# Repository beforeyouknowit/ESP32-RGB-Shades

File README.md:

# ESP32 RGB Shades

This repo currently represents an electronics update, based on the  ESP32 Pico Mini, as a redesign of [macetech/RGBShades](https://github.com/macetech/RGBShades) from 2015.

I was one of the Kickstarter backers of macetech's original campaign for "RGB Shades", described here: https://www.kickstarter.com/projects/macetech/rgb-led-shades

Redesigned in KiCad 8.x, based on original Eagle files from Macetech's website.

## Features
New electronics include:
- USB-C PD via STUSB4500 IC, which negotiates with USB-C PD supplies (e.g. modern power bank batteries and wall adapters) for 20V output, up to 5A, or 100W.
- TDK ICS-43434 microphone, with I2S digital output, for onboard audio analysis and beat detection.
- Jumper for selecting microphone digital output as left (default) or right channel audio over I2S.
- 5V, 1.5A linear voltage regulator for powering WS2812B LEDs from 20V USB-C PD supply.
- 3.3V, 1.0A linear voltage regulator for powering onboard ICs.
- Slight changes to rear ear-stem geometry to accommodate new USB-C PD IC and passives.

What hasn't changed:
- Same power switch.
- Same pushbuttons. (Now labeled as "Animate" and "Brightness".)
- Same CP2102N USB to UART, with "full remote reset" capabilities, making firmware flashing just as easy.
- Same 0.1" (DuPont connector/header) through-holes for direct CP2102N debug, e.g. for bypassing USB.
- Same JST connector to existing RGBShades display, i.e. the front part of the glasses assembly.
- Same glasses assembly hardware positions; meant as a direct upgrade for existing RGBShades owners.

## License
This project is licensed under CERN-OHL-S 2.0 or later version. See the LICENSE file for details.

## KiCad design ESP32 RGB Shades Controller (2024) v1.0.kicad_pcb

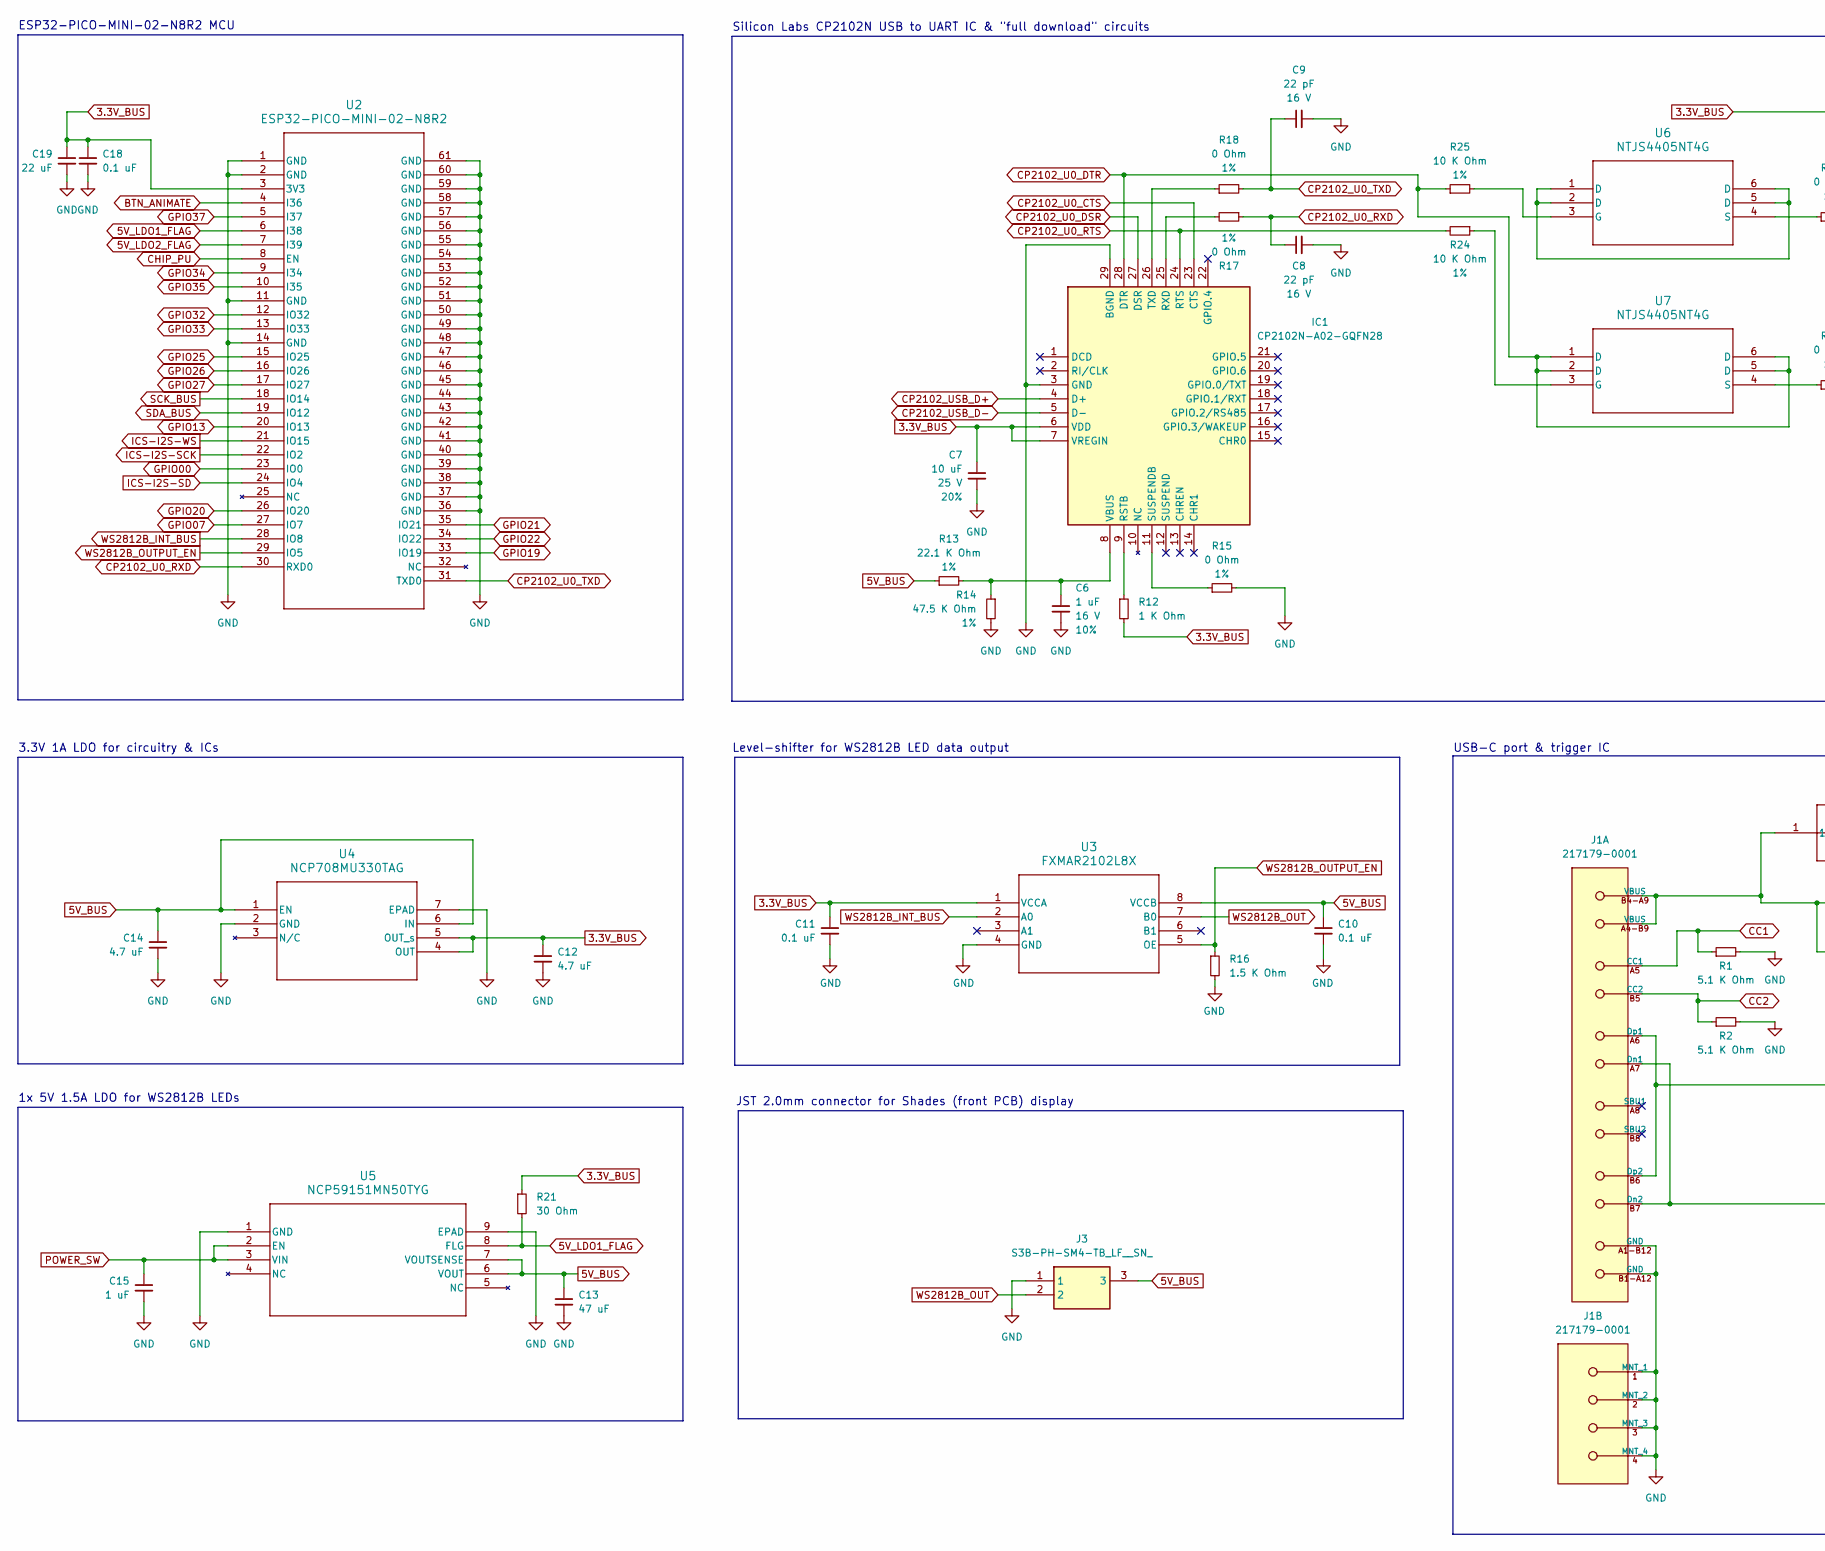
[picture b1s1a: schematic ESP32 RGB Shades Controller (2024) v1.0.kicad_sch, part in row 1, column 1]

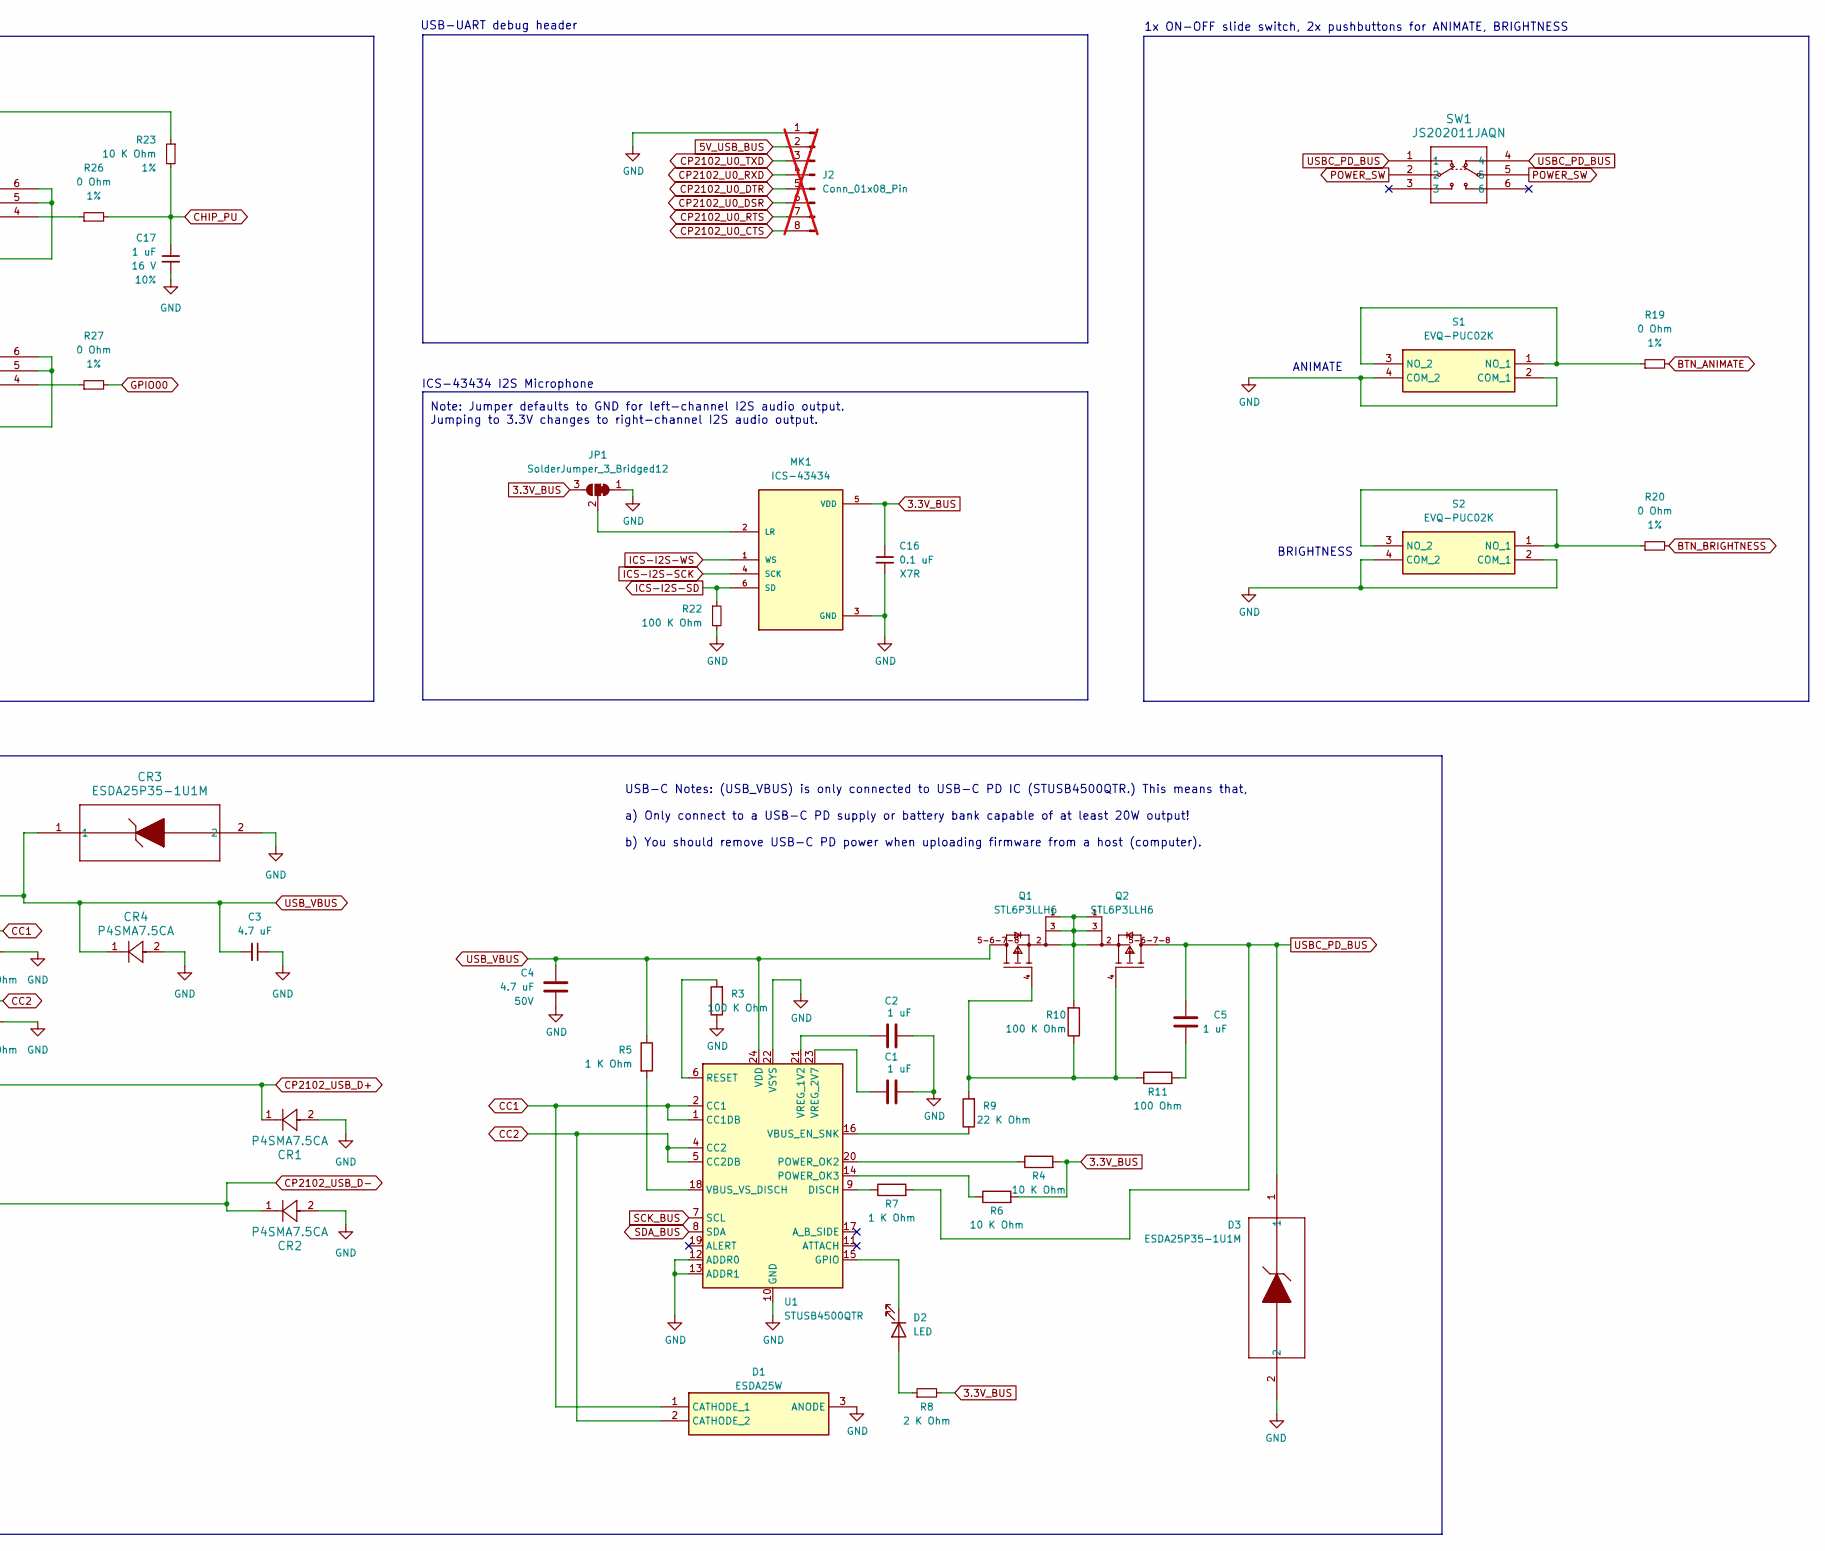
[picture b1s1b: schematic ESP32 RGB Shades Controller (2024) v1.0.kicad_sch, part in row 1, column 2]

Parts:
C1, C2, C5: 1 uF; C_0805_2012Metric; MPN1 CC0805KRX7R7BB104
C3, C12, C14: 4.7 uF; C_0805_2012Metric
C4: 4.7 uF; C_0805_2012Metric; Voltage 50V; MPN1 CC0805KRX7R7BB104
C6, C17: 1 uF; C_0805_2012Metric; Voltage 16 V; Tolerance 10%
C7: 10 uF; C_0805_2012Metric; Voltage 25 V; Tolerance 20%
C8, C9: 22 pF; C_0805_2012Metric; Voltage 16 V
C10, C11, C16, C18: 0.1 uF; C_0805_2012Metric
C13: 47 uF; C_0805_2012Metric
C15: 1 uF; C_0805_2012Metric
C19: 22 uF; C_0805_2012Metric
CR1, CR2, CR4: P4SMA7.5CA; P4SMASeries_LTF
CR3: ESDA25P35-1U1M; ESDA25P351U1M
D1: ESDA25W; SOT323-3L_STM; Manufacturer_Part_Number ESDA25W; Mouser Part Number 511-ESDA25W
D2: LED; LED_0805_2012Metric
D3: ESDA25P35-1U1M; ESDA25P351U1M; Manufacturer_Part_Number ESDA25P35-1U1M; Mouser Part Number 511-ESDA25P35-1U1M
IC1: CP2102N-A02-GQFN28; QFN50P500X500X80-29N-D; Manufacturer_Part_Number CP2102N-A02-GQFN28; Mouser Part Number 634-CP2102NA02GQFN28
J1: 217179-0001; Molex-217179-0001-MFG; current rating 1.25A; voltage rating 30V; mouser part number 538-217179-0001; digikey description CONN RCP USB2.0 TYP C 24P SMD RA
J2: Conn_01x08_Pin; PinHeader_1x08_P2.54mm_Vertical; not fitted
J3: S3B-PH-SM4-TB_LF__SN_; S3B-PH-SM4-TB; Manufacturer_Part_Number S3B-PH-SM4-TB(LF)(SN)
JP1: SolderJumper_3_Bridged12; SolderJumper-3_P1.3mm_Bridged2Bar12_Pad1.0x1.5mm_NumberLabe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
MK1: ICS-43434; MIC_ICS-43434
Q1, Q2: STL6P3LLH6; STMicroelectronics-PowerFLAT3.3x3.3-8465286-0-2-MFG; mouser part number 511-STL6P3LLH6; digikey description MOSFET P-CH 30V 6A POWERFLAT
R1, R2: 5.1 K Ohm; R_0805_2012Metric
R3, R10, R22: 100 K Ohm; R_0805_2012Metric
R4, R6: 10 K Ohm; R_0805_2012Metric
R5, R7, R12: 1 K Ohm; R_0805_2012Metric
R8: 2 K Ohm; R_0805_2012Metric
R9: 22 K Ohm; R_0805_2012Metric
R11: 100 Ohm; R_0805_2012Metric
R13: 22.1 K Ohm; R_0805_2012Metric; Tolerance 1%
R14: 47.5 K Ohm; R_0805_2012Metric; Tolerance 1%
R15, R17, R18, R19, R20, R26, R27: 0 Ohm; R_0805_2012Metric; Tolerance 1%
R16: 1.5 K Ohm; R_0805_2012Metric
R21: 30 Ohm; R_0805_2012Metric
R23, R24, R25: 10 K Ohm; R_0805_2012Metric; Tolerance 1%
S1, S2: EVQ-PUC02K; EVQPUC02K; Manufacturer_Part_Number EVQ-PUC02K; Mouser Part Number 667-EVQ-PUC02K
SW1: JS202011JAQN; SW_DPDT_CK_JS202011JCQN
U1: STUSB4500QTR; QFN50P400X400X100-25N-D
U2: ESP32-PICO-MINI-02-N8R2; ESP32-PICO-MINI-02_EXP
U3: FXMAR2102L8X; FXMAR2102L8X_ONS-M
U4: NCP708MU330TAG; UDFN6_3X3_ONS-M
U5: NCP59151MN50TYG; DFN8_ONS-M
U6, U7: NTJS4405NT4G; SOT-363-6_2P2X1P35_ONS-M

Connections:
3.3V_BUS: C7.1, C11.1, C12.1, C16.1, C18.1, C19.1, IC1.6 (VDD), IC1.7 (VREGIN), JP1.3 (B), MK1.5 (VDD), R4.2, R6.2, R8.2, R12.2, R21.1, R23.1, U2.3 (3V3), U3.1 (VCCA), U4.4 (OUT), U4.5 (OUT_s)
5V_BUS: C10.1, C13.1, C14.1, J3.3, R13.1, U3.8 (VCCB), U4.1 (EN), U4.6 (IN), U5.6 (VOUT), U5.7 (VOUTSENSE)
5V_LDO1_FLAG: R21.2, U2.6 (I38), U5.8 (FLG)
5V_LDO2_FLAG: U2.7 (I39)
5V_USB_BUS: J2.2
BTN_ANIMATE: R19.2, U2.4 (I36)
BTN_BRIGHTNESS: R20.2
CC1: D1.1 (CATHODE_1), J1.A5 (CC1), R1.1, U1.1 (CC1DB), U1.2 (CC1)
CC2: D1.2 (CATHODE_2), J1.B5 (CC2), R2.1, U1.4 (CC2), U1.5 (CC2DB)
CHIP_PU: C17.1, R23.2, R26.2, U2.8 (EN)
CP2102_U0_CTS: IC1.23 (CTS), J2.8
CP2102_U0_DSR: IC1.27 (DSR), J2.6
CP2102_U0_DTR: IC1.28 (DTR), J2.5, R25.1, U7.1 (D), U7.2 (D), U7.5 (D), U7.6 (D)
CP2102_U0_RTS: IC1.24 (RTS), J2.7, R24.2
CP2102_U0_RXD: C8.1, J2.4, R17.1, U2.30 (RXD0)
CP2102_U0_TXD: C9.1, J2.3, R18.2, U2.31 (TXD0)
CP2102_USB_D+: CR1.1, IC1.4 (D+), J1.A6 (Dp1), J1.B6 (Dp2)
CP2102_USB_D-: CR2.1, IC1.5 (D-), J1.A7 (Dn1), J1.B7 (Dn2)
GND: C1.2, C2.2, C3.1, C4.2, C6.2, C7.2, C8.2, C9.2, C10.2, C11.2, C12.2, C13.2, C14.2, C15.2, C16.2, C17.2, C18.2, C19.2, CR1.2, CR2.2, CR3.2, CR4.2, D1.3 (ANODE), D3.2, IC1.3 (GND), IC1.29 (BGND), J1.1 (MNT_1), J1.2 (MNT_2), J1.3 (MNT_3), J1.4 (MNT_4), J1.A1-B12 (GND), J1.B1-A12 (GND), J2.1, J3.1, JP1.1 (A), MK1.3 (GND), R1.2, R2.2, R3.1, R14.2, R15.2, R16.2, R22.2, S1.2 (COM_1), S1.4 (COM_2), S2.2 (COM_1), S2.4 (COM_2), U1.10 (GND), U1.12 (ADDR0), U1.13 (ADDR1), U1.22 (VSYS), U1.25 (GND), U2.1 (GND), U2.2 (GND), U2.11 (GND), U2.14 (GND), U2.36 (GND), U2.37 (GND), U2.38 (GND), U2.39 (GND), U2.40 (GND), U2.41 (GND), U2.42 (GND), U2.43 (GND), U2.44 (GND), U2.45 (GND), U2.46 (GND), U2.47 (GND), U2.48 (GND), U2.49 (GND), U2.50 (GND), U2.51 (GND), U2.52 (GND), U2.53 (GND), U2.54 (GND), U2.55 (GND), U2.56 (GND), U2.57 (GND), U2.58 (GND), U2.59 (GND), U2.60 (GND), U2.61 (GND), U3.4 (GND), U4.2 (GND), U4.7 (EPAD), U5.1 (GND), U5.9 (EPAD)
GPIO00: R27.2, U2.23 (IO0)
GPIO07: U2.27 (IO7)
GPIO13: U2.20 (IO13)
GPIO19: U2.33 (IO19)
GPIO20: U2.26 (IO20)
GPIO21: U2.35 (IO21)
GPIO22: U2.34 (IO22)
GPIO25: U2.15 (IO25)
GPIO26: U2.16 (IO26)
GPIO27: U2.17 (IO27)
GPIO32: U2.12 (IO32)
GPIO33: U2.13 (IO33)
GPIO34: U2.9 (I34)
GPIO35: U2.10 (I35)
GPIO37: U2.5 (I37)
ICS-I2S-SCK: MK1.4 (SCK), U2.22 (IO2)
ICS-I2S-SD: MK1.6 (SD), R22.1, U2.24 (IO4)
ICS-I2S-WS: MK1.1 (WS), U2.21 (IO15)
unnamed: C5.1, R11.2
unnamed: D2.2 (A), R8.1
unnamed: D2.1 (K), U1.15 (GPIO)
unnamed: IC1.9 (RSTB), R12.1
unnamed: IC1.25 (RXD), R17.2
unnamed: IC1.11 (SUSPENDB), R15.1
unnamed: IC1.26 (TXD), R18.1
unnamed: C6.1, IC1.8 (VBUS), R13.2, R14.1
unnamed: JP1.2 (C), MK1.2 (LR)
unnamed: Q1.4 (G), Q2.4 (G), R9.2, R10.1, R11.1
unnamed: Q1.1 (S), Q1.2 (S), Q1.3 (S), Q2.1 (S), Q2.2 (S), Q2.3 (S), R10.2
unnamed: R19.1, S1.1 (NO_1), S1.3 (NO_2)
unnamed: R20.1, S2.1 (NO_1), S2.3 (NO_2)
unnamed: R7.1, U1.9 (DISCH)
unnamed: R4.1, U1.20 (POWER_OK2)
unnamed: R6.1, U1.14 (POWER_OK3)
unnamed: R3.2, U1.6 (RESET)
unnamed: R9.1, U1.16 (VBUS_EN_SNK)
unnamed: R5.2, U1.18 (VBUS_VS_DISCH)
unnamed: C2.1, U1.21 (VREG_1V2)
unnamed: C1.1, U1.23 (VREG_2V7)
unnamed: U6.1 (D), U6.2 (D), U6.5 (D), U6.6 (D)
unnamed: R25.2, U6.3 (G)
unnamed: R26.1, U6.4 (S)
unnamed: R24.1, U7.3 (G)
unnamed: R27.1, U7.4 (S)
POWER_SW: C15.1, SW1.2, SW1.5, U5.2 (EN), U5.3 (VIN)
SCK_BUS: U1.7 (SCL), U2.18 (IO14)
SDA_BUS: U1.8 (SDA), U2.19 (IO12)
USBC_PD_BUS: C5.2, D3.1, Q2.5-6-7-8 (D), R7.2, SW1.1, SW1.4
USB_VBUS: C3.2, C4.1, CR3.1, CR4.1, J1.A4-B9 (VBUS), J1.B4-A9 (VBUS), Q1.5-6-7-8 (D), R5.1, U1.24 (VDD)
WS2812B_INT_BUS: U2.28 (IO8), U3.2 (A0)
WS2812B_OUT: J3.2, U3.7 (B0)
WS2812B_OUTPUT_EN: R16.1, U2.29 (IO5), U3.5 (OE)

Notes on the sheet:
JST 2.0mm connector for Shades (front PCB) display
USB-C Notes: (USB_VBUS) is only connected to USB-C PD IC (STUSB4500QTR.) This means that, a) Only connect to a USB-C PD supply or battery bank capable of at least 20W output! b) You should remove USB-C PD power when uploading firmware from a host (computer).
Silicon Labs CP2102N USB to UART IC & "full download" circuits
1x 5V 1.5A LDO for WS2812B LEDs
USB-C port & trigger IC
Note: Jumper defaults to GND for left-channel I2S audio output. Jumping to 3.3V changes to right-channel I2S audio output.
ANIMATE
ICS-43434 I2S Microphone
Level-shifter for WS2812B LED data output
3.3V 1A LDO for circuitry & ICs
ESP32-PICO-MINI-02-N8R2 MCU
BRIGHTNESS
USB-UART debug header
1x ON-OFF slide switch, 2x pushbuttons for ANIMATE, BRIGHTNESS

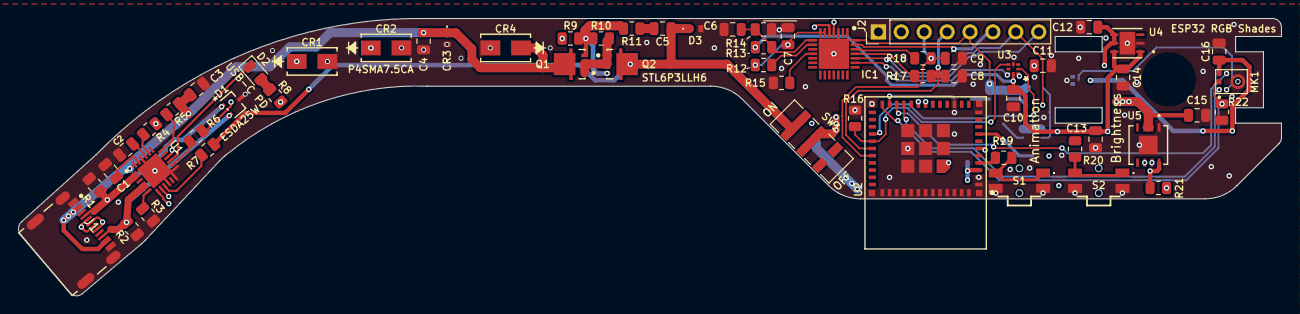
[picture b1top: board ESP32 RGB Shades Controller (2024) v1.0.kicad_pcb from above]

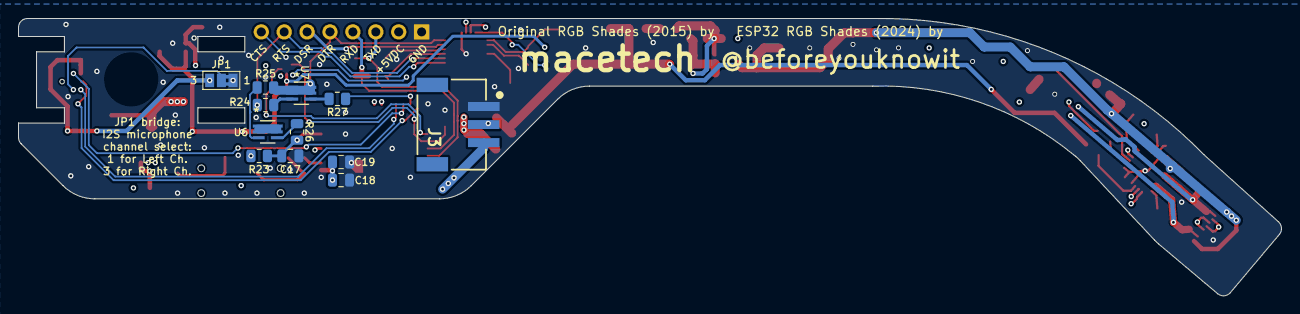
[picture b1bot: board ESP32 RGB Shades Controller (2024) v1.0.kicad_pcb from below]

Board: 4 copper layers, 140.1 x 30.8 mm, 71 parts (12 on the bottom side), 54 nets.

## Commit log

2024-06-27 Initial repo commit with v1.0 design.
2024-06-27 Resolved merge conflicts.
2024-06-27 Saved previous LED XY map.
2024-06-27 Update README.md to include renders of PCB.
